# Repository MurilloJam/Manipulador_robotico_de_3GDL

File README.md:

# Manipulador_robotico_de_3GDL
## Diseño, modelado y construcción
En este repositorio se almacenan los archivos de diseño, modelado y simulación de un manipualdor robótico de 3 GDL partiendo del diseño de una fuente de alimentación lineal con sus fases elementales: reducción, rectificación, filtrado, regulación y variación de carga.
Conforme se avance en el proyecto se podrá encontrar el conjunto de especificaciones y avance detallando cada mejora o complemento agregado.
## Comenzando
Estas instrucciones te permitirán obtener una copia del proyecto en funcionamiento en tu máquina local para propósitos de desarrollo y pruebas.
### Requisitos
Antes de montar el proyecto localmente se debe asegurar que se cuentan con los siguientes softwares necesarios para funcionar o realizar modificaciones.
- Multisim en su versión 14.0
- Eagle 
- Fushion 360
- FlatCAM en su versión 8.994

## Estructura del proyecto
La composición del proyecto esta constituida por dos fases. Cada fase es independiente una de otra y se ejecutan para diferentes propósitos:
- Fase **PowerSupply**: Consiste en el diseño exclusivo de la fuente de alimentación que suministrará la energía al manipulador. Todos sus archivos referentes se encontrarán en la carpeta PowerSupply.
- Fase **3 GDL**: Consiste en el diseño y simulación del manipulador una vez se ha satisfecho la composición de la fuente de alimentación. En esta fase se presentará la lógica de control y el análisis cinemático del manipulador pudiendo visualizar los archivos desde el directorio 3 GDL.

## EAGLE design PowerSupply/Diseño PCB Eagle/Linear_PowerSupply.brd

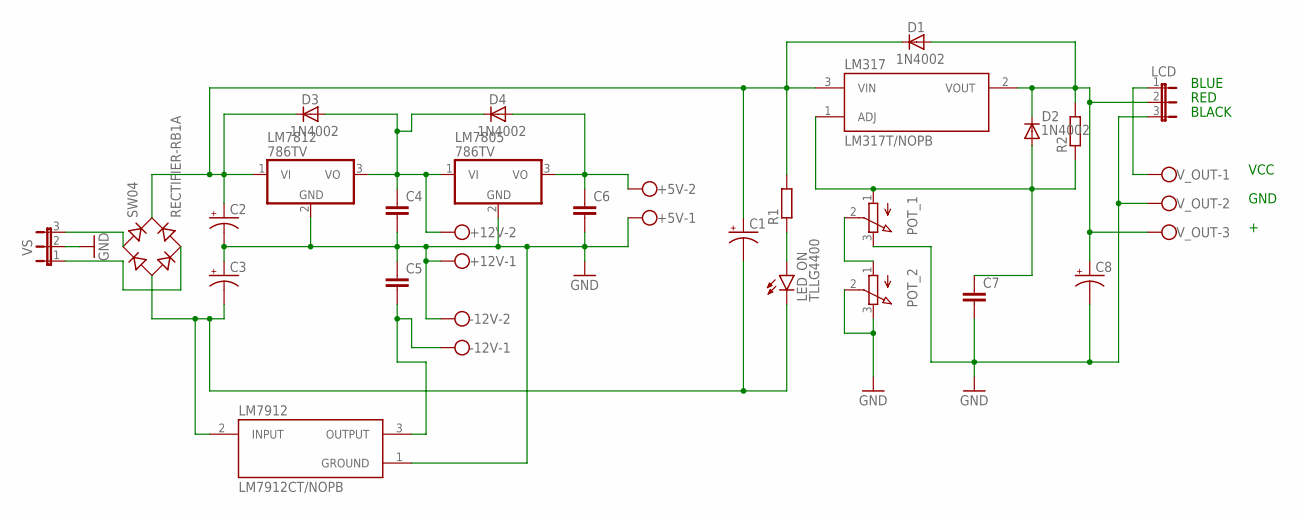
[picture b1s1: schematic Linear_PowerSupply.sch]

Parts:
+5V, +12V: W237-102
-12V: W237-102
C1: CPOL-USE5-13; E5-13
C2, C3, C8: CPOL-USE3.5-8; E3,5-8
C4, C5, C6, C7: C-EU025-024X044; C025-024X044
D1, D2, D3, D4: 1N4002; DO41-10
LCD: JP2E; JP2
LED_ON: TLLG4400; LED3MM
LM317: LM317T/NOPB; LM317T/NOPB_TO254P1054X470X1955-3
LM7805, LM7812: 786TV; TO220V
LM7912: LM7912CT/NOPB; TO254P1054X470X1955-3
POT_1, POT_2: 3RP/1610N
R1, R2: R-EU_0207/10; 0207/10
SW04: RECTIFIER-RB1A; RB1A
VS: JP2E; JP2
V_OUT: W237-103

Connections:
GND: +5V.1, +12V.1, -12V.2, C2.-, C3.+, C4.2, C5.1, C6.2, C7.2, C8.-, LCD.3, LM7805.2 (GND), LM7812.2 (GND), LM7912.1 (GROUND), POT_1.3 (E), POT_2.2 (S), POT_2.3 (E), VS.2, V_OUT.2
unnamed: LED_ON.A, R1.1
unnamed: C7.1, D2.A, LM317.1 (ADJ), POT_1.1 (A), R2.1
unnamed: LCD.1, V_OUT.1
unnamed: C8.+, D1.A, D2.C, LCD.2, LM317.2 (VOUT), R2.2, V_OUT.3
unnamed: C1.+, C2.+, D1.C, D3.C, LM317.3 (VIN), LM7812.1 (VI), R1.2, SW04.+
unnamed: C1.-, C3.-, LED_ON.K (C), LM7912.2 (INPUT), SW04.-
unnamed: POT_1.2 (S), POT_2.1 (A)
unnamed: -12V.1, C5.2, LM7912.3 (OUTPUT)
unnamed: +12V.2, C4.1, D3.A, D4.C, LM7805.1 (VI), LM7812.3 (VO)
unnamed: +5V.2, C6.1, D4.A, LM7805.3 (VO)
VAC+: SW04.AC1, VS.3
VAC-: SW04.AC2, VS.1

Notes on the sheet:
RED
BLACK
BLUE
VCC
GND

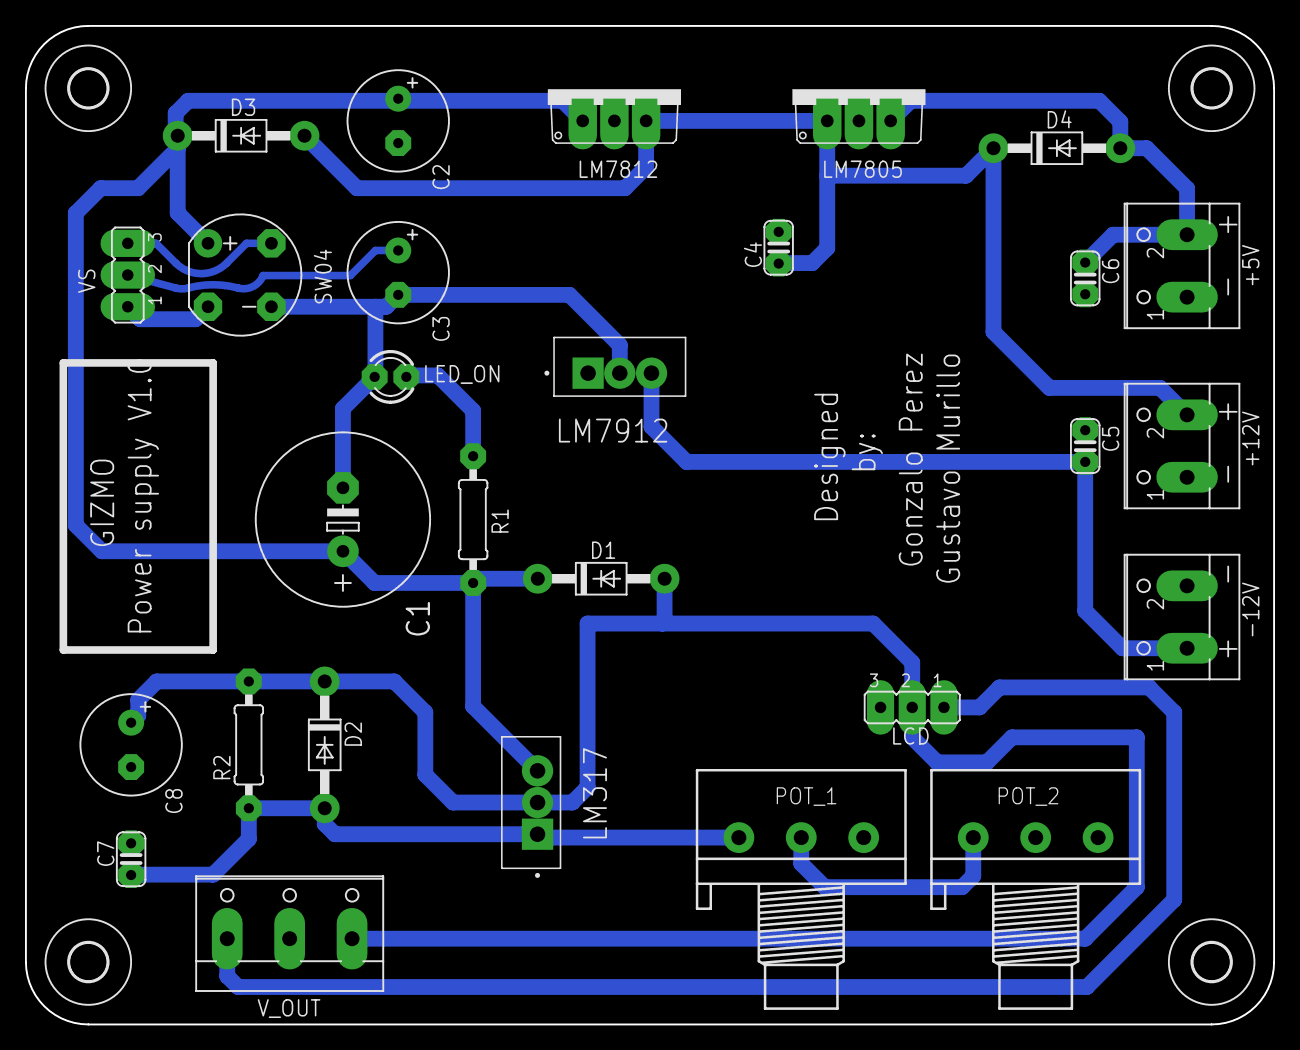
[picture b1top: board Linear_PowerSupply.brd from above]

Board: 2 copper layers, 100.0 x 80.0 mm, 32 parts (0 on the bottom side), 13 nets.

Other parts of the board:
U$1, U$2, U$3, U$4: 3,0

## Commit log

2021-10-04 add Fuente lineal V1.0 Se ha agregado el modelo SPICE de la fuente de alimentación lineal diseñado en el software Multisim en su version 14.0. Esta primera version considera 3 modulos esenciales: Ten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
2021-10-19 add Eagle schematic design for PCB Se ha añadido el esquema Eagle de conexion de la fuente de alimentacion que permitira definir los footprints de la PCB.
2021-10-19 add Eagle PCB Board design V1.0 Se ha añadido el diseño de la tarjeta PCB que se implementara para el proyecto. Se anexan 2 imagenes del modelo final esperado.
2021-10-19 add Gerber Files Se comparten los ficheros Gerber necesarios para proceder con el maquinado de la tarjeta PCB. Durante el diseño las pistas se definieron en el archivo copper_bottom.grb y el grabado 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
2021-10-19 add CNC Files Se han agregado los archivos necesarios para proceder con el mecanizado de la tarjeta PCB. Se comparten los archivos DXF en caso de requerirse una modificación rapida y el codigo G para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
2021-10-23 update PCB pads design Se ha actualizado el archivo Eagle correspondiente al diseño de los pads de la tarjeta impresa. Dentro de los cambios se ha aumentado el tamaño de cada terminal. Es importante 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
2021-10-23 add Modelo Fushion360 Se ha agregado el modelo 3D de la fuente propuesta diseñado en Fushion360. En este modelo se presentan las dimensiones reales y el conjunto de componentes por emplear, como las 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
2021-10-24 update CNC File Se ha modificado el codigo G del maquinado de la PCB. En esta modificacion se ha resuelto la problematica de eliminar cobre en terminales donde existe tierra comun. Sin embargo, ante 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
2021-10-24 add Silkscreen CNC File Se ha agregado el script en codigo G para el grabado superior de la serigrafia del conjunto de componentes. Resta verificar que la fresa sea capaz de generar el grabado.
2021-11-10 update Gerber Files Se ha actualizado el fichero Gerber de la tarjeta. En esta modificacion se ha redimensionado cada bus de comunicacion y los anillos de union. Las nuevas dimensiones consideran un 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
2021-11-10 add Gerber Images
2021-11-13 add mobile code Se ha agregado la clase principal para el control del robot movil encargado de transportar las cargas por emplear.
2021-11-28 add LabView UI El siguiente archivo es la primer versión del programa en LabView que permitirá leer y escribir datos a Arduino. Es importante hacer pruebas con el modelo completamente ensamblado y ve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
